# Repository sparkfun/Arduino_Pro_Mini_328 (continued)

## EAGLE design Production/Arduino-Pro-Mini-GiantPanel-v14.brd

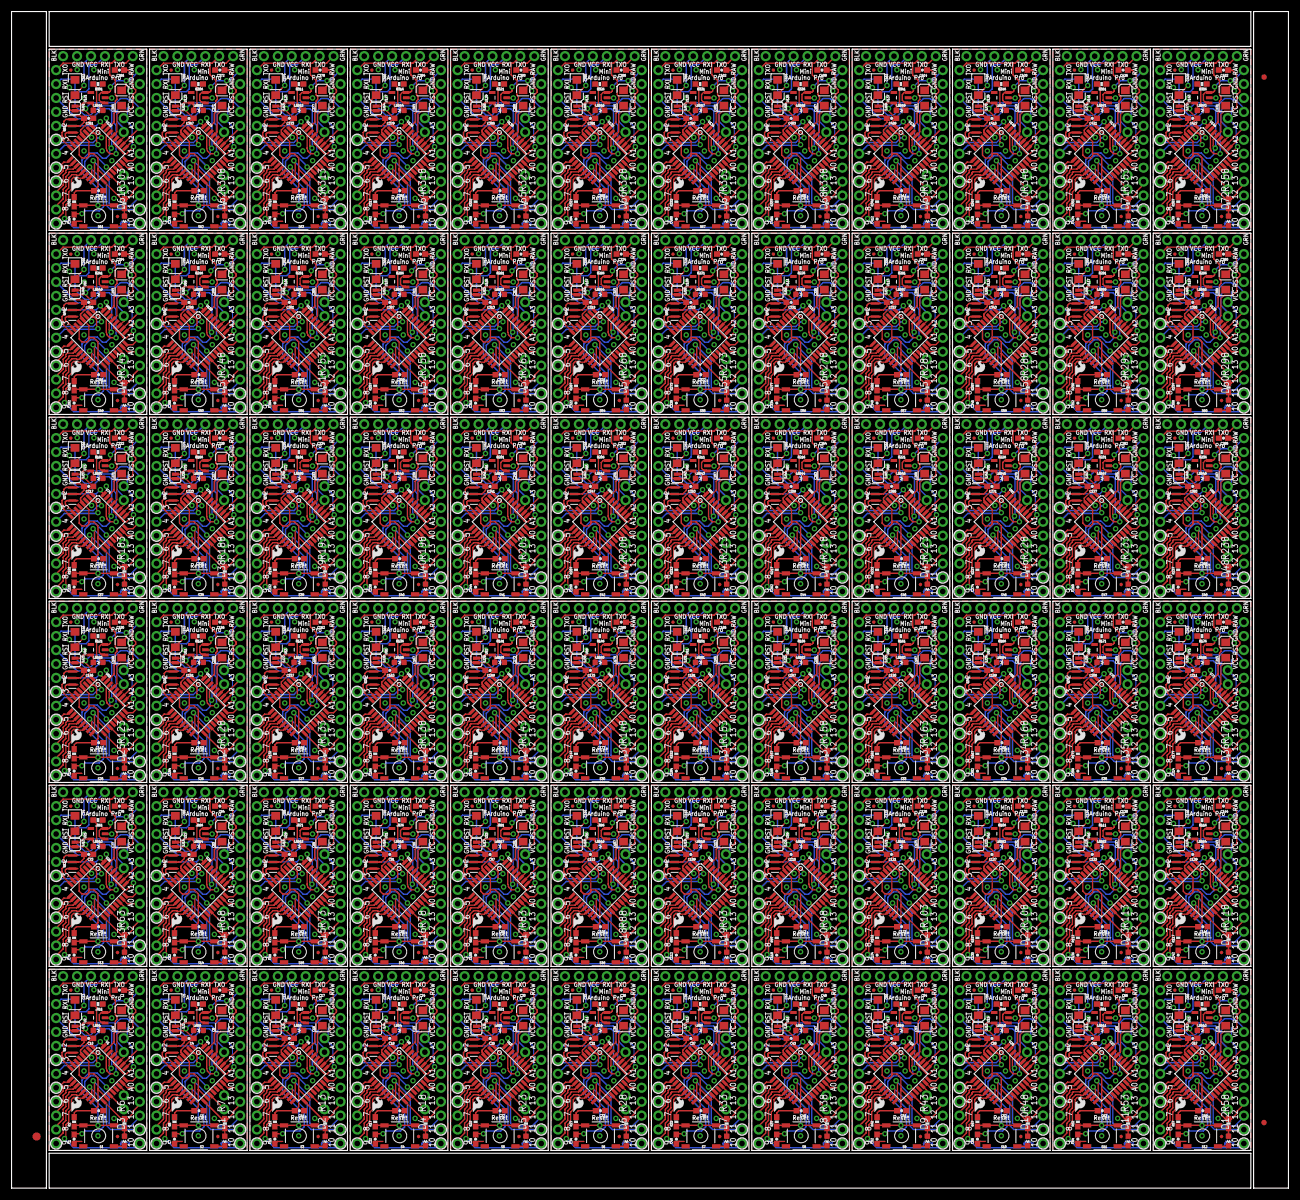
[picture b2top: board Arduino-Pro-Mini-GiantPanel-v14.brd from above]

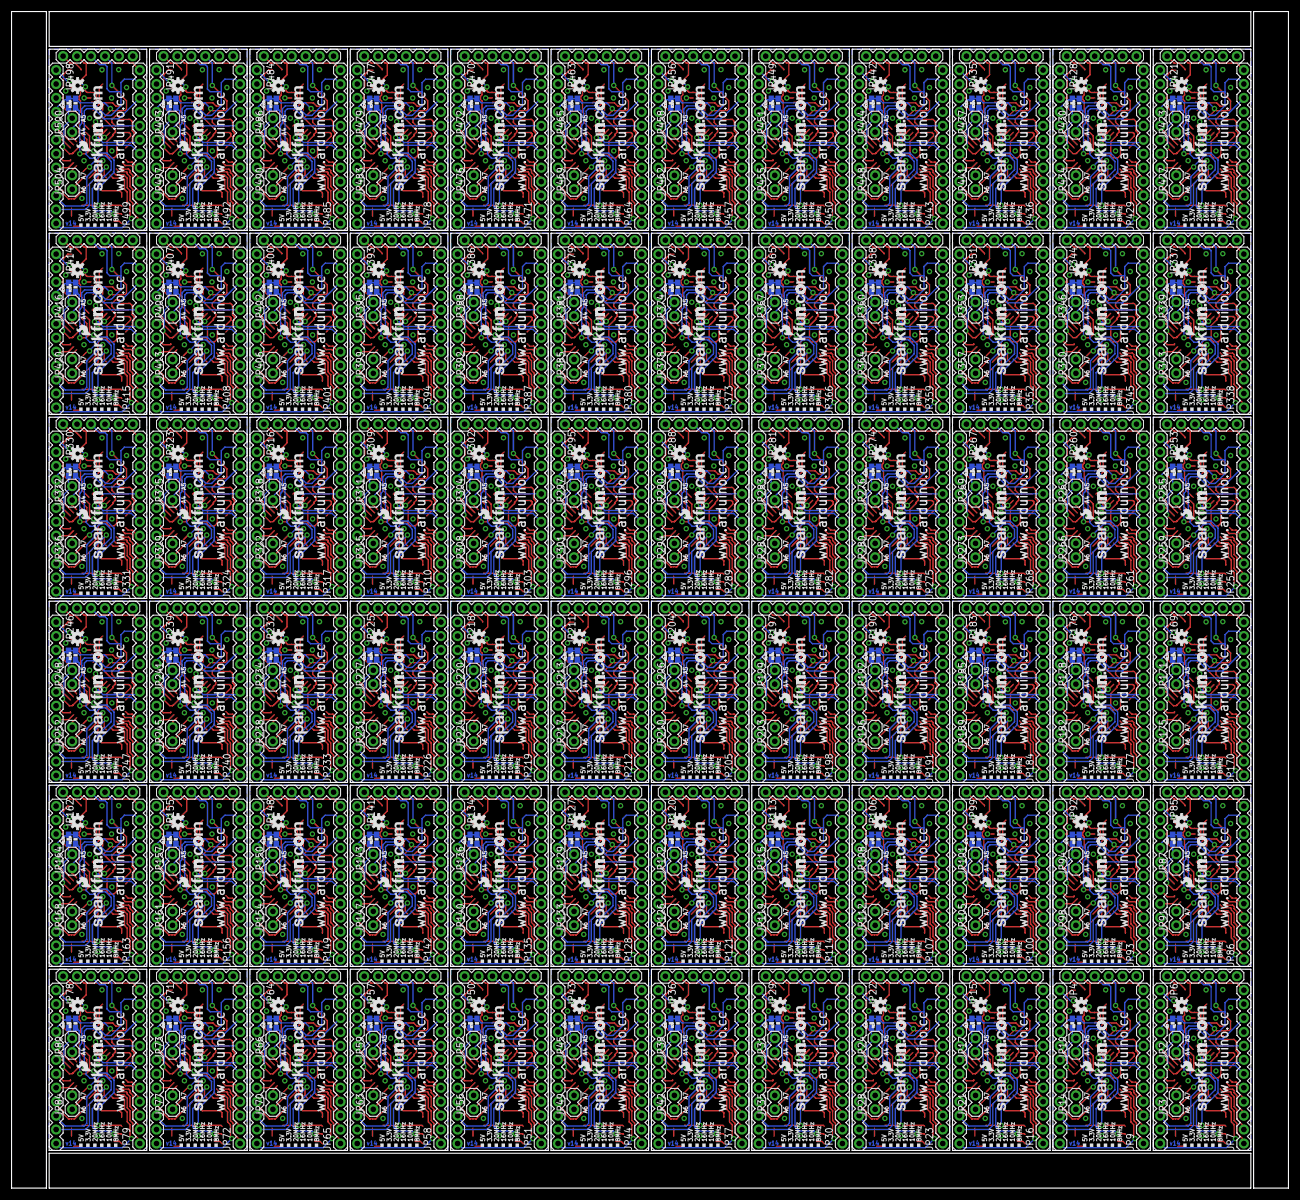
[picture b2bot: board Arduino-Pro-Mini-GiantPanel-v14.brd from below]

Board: 2 copper layers, 232.7 x 214.4 mm, 2019 parts (648 on the bottom side), 2376 nets.

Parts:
C1, C2, C3, C4, C6, C7, C9, C10, C11, C14, C15, C17, C18, C21, C22, C24, C25, C27, C28, C30, C31, C33, C34, C36, C37, C39, C40, C42, C43, C45, C46, C48, C49, C51, C52, C54, C55, C57, C58, C60, C61, C63, C64, C66, C67, C69, C70, C72, C73, C75, C76, C78, C79, C81, C82, C84, C85, C87, C88, C90, C91, C93, C94, C96, C97, C99, C100, C102, C103, C105, C106, C108, C109, C111, C112, C114, C115, C117, C118, C120, C121, C123, C124, C126, C127, C129, C130, C132, C133, C135, C136, C138, C139, C141, C142, C144, C145, C147, C148, C150, C151, C153, C154, C156, C157, C159, C160, C162, C163, C165, C166, C168, C169, C171, C172, C174, C175, C177, C178, C180, C181, C183, C184, C186, C187, C189, C190, C192, C193, C195, C196, C198, C199, C201, C202, C204, C205, C207, C208, C210, C211, C213, C214, C216, C217, C219, C220, C222, C223, C225, C226, C228, C229, C231, C232, C234, C235, C237, C238, C240, C241, C243, C244, C246, C247, C249, C250, C252, C253, C255, C256, C258, C259, C261, C262, C264, C265, C267, C268, C270, C271, C273, C274, C276, C277, C279, C280, C282, C283, C285, C286, C288, C289, C291, C292, C294, C295, C297, C298, C300, C301, C303, C304, C306, C307, C309, C310, C312, C313, C315, C316, C318, C319, C321, C322, C324, C325, C327, C328, C330, C331, C333, C334, C336, C337, C339, C340, C342, C343, C345, C346, C348, C349, C351, C352, C354, C355, C357, C358, C360, C361, C363, C364, C366, C367, C369, C370, C372, C373, C375, C376, C378, C379, C381, C382, C384, C385, C387, C388, C390, C391, C393, C394, C396, C397, C399, C400, C402, C403, C405, C406, C408, C409, C411, C412, C414, C415, C417, C418, C420, C421, C423, C424, C426, C427, C429, C430, C432: 0.1uF; 0603-CAP
C5, C8, C12, C13, C16, C19, C20, C23, C26, C29, C32, C35, C38, C41, C44, C47, C50, C53, C56, C59, C62, C65, C68, C71, C74, C77, C80, C83, C86, C89, C92, C95, C98, C101, C104, C107, C110, C113, C116, C119, C122, C125, C128, C131, C134, C137, C140, C143, C146, C149, C152, C155, C158, C161, C164, C167, C170, C173, C176, C179, C182, C185, C188, C191, C194, C197, C200, C203, C206, C209, C212, C215, C218, C221, C224, C227, C230, C233, C236, C239, C242, C245, C248, C251, C254, C257, C260, C263, C266, C269, C272, C275, C278, C281, C284, C287, C290, C293, C296, C299, C302, C305, C308, C311, C314, C317, C320, C323, C326, C329, C332, C335, C338, C341, C344, C347, C350, C353, C356, C359, C362, C365, C368, C371, C374, C377, C380, C383, C386, C389, C392, C395, C398, C401, C404, C407, C410, C413, C416, C419, C422, C425, C428, C431: 10uF; EIA3216
D1, D2, D3, D4, D5, D6, D7, D8, D9, D10, D11, D12, D13, D14, D15, D16, D17, D18, D19, D20, D21, D22, D23, D24, D25, D26, D27, D28, D29, D30, D31, D32, D33, D34, D35, D36, D37, D38, D39, D40, D41, D42, D43, D44, D45, D46, D47, D48, D49, D50, D51, D52, D53, D54, D55, D56, D57, D58, D59, D60, D61, D62, D63, D64, D65, D66, D67, D68, D69, D70, D71, D72: Green; 0603-LED-ALT1
E$1: FIDUCIAL-1.5X3
E$4, E$6: FIDUCIAL-1X2
JP1, JP11, JP18, JP25, JP32, JP39, JP46, JP53, JP60, JP67, JP74, JP81, JP88, JP95, JP102, JP109, JP116, JP123, JP130, JP137, JP144, JP151, JP158, JP165, JP172, JP179, JP186, JP193, JP200, JP207, JP214, JP221, JP228, JP235, JP242, JP249, JP256, JP263, JP270, JP277, JP284, JP291, JP298, JP305, JP312, JP319, JP326, JP333, JP340, JP347, JP354, JP361, JP368, JP375, JP382, JP389, JP396, JP403, JP410, JP417, JP424, JP431, JP438, JP445, JP452, JP459, JP466, JP473, JP480, JP487, JP494, JP501: FTDI Basic; 1X06
JP2, JP3, JP10, JP14, JP17, JP21, JP24, JP28, JP31, JP35, JP38, JP42, JP45, JP49, JP52, JP56, JP59, JP63, JP66, JP70, JP73, JP77, JP80, JP84, JP87, JP91, JP94, JP98, JP101, JP105, JP108, JP112, JP115, JP119, JP122, JP126, JP129, JP133, JP136, JP140, JP143, JP147, JP150, JP154, JP157, JP161, JP164, JP168, JP171, JP175, JP178, JP182, JP185, JP189, JP192, JP196, JP199, JP203, JP206, JP210, JP213, JP217, JP220, JP224, JP227, JP231, JP234, JP238, JP241, JP245, JP248, JP252, JP255, JP259, JP262, JP266, JP269, JP273, JP276, JP280, JP283, JP287, JP290, JP294, JP297, JP301, JP304, JP308, JP311, JP315, JP318, JP322, JP325, JP329, JP332, JP336, JP339, JP343, JP346, JP350, JP353, JP357, JP360, JP364, JP367, JP371, JP374, JP378, JP381, JP385, JP388, JP392, JP395, JP399, JP402, JP406, JP409, JP413, JP416, JP420, JP423, JP427, JP430, JP434, JP437, JP441, JP444, JP448, JP451, JP455, JP458, JP462, JP465, JP469, JP472, JP476, JP479, JP483, JP486, JP490, JP493, JP497, JP500, JP504: 1X02
JP4, JP6, JP7, JP9, JP15, JP16, JP22, JP23, JP29, JP30, JP36, JP37, JP43, JP44, JP50, JP51, JP57, JP58, JP64, JP65, JP71, JP72, JP78, JP79, JP85, JP86, JP92, JP93, JP99, JP100, JP106, JP107, JP113, JP114, JP120, JP121, JP127, JP128, JP134, JP135, JP141, JP142, JP148, JP149, JP155, JP156, JP162, JP163, JP169, JP170, JP176, JP177, JP183, JP184, JP190, JP191, JP197, JP198, JP204, JP205, JP211, JP212, JP218, JP219, JP225, JP226, JP232, JP233, JP239, JP240, JP246, JP247, JP253, JP254, JP260, JP261, JP267, JP268, JP274, JP275, JP281, JP282, JP288, JP289, JP295, JP296, JP302, JP303, JP309, JP310, JP316, JP317, JP323, JP324, JP330, JP331, JP337, JP338, JP344, JP345, JP351, JP352, JP358, JP359, JP365, JP366, JP372, JP373, JP379, JP380, JP386, JP387, JP393, JP394, JP400, JP401, JP407, JP408, JP414, JP415, JP421, JP422, JP428, JP429, JP435, JP436, JP442, JP443, JP449, JP450, JP456, JP457, JP463, JP464, JP470, JP471, JP477, JP478, JP484, JP485, JP491, JP492, JP498, JP499: 1X12
JP5, JP8, JP12, JP13, JP19, JP20, JP26, JP27, JP33, JP34, JP40, JP41, JP47, JP48, JP54, JP55, JP61, JP62, JP68, JP69, JP75, JP76, JP82, JP83, JP89, JP90, JP96, JP97, JP103, JP104, JP110, JP111, JP117, JP118, JP124, JP125, JP131, JP132, JP138, JP139, JP145, JP146, JP152, JP153, JP159, JP160, JP166, JP167, JP173, JP174, JP180, JP181, JP187, JP188, JP194, JP195, JP201, JP202, JP208, JP209, JP215, JP216, JP222, JP223, JP229, JP230, JP236, JP237, JP243, JP244, JP250, JP251, JP257, JP258, JP264, JP265, JP271, JP272, JP278, JP279, JP285, JP286, JP292, JP293, JP299, JP300, JP306, JP307, JP313, JP314, JP320, JP321, JP327, JP328, JP334, JP335, JP341, JP342, JP348, JP349, JP355, JP356, JP362, JP363, JP369, JP370, JP376, JP377, JP383, JP384, JP390, JP391, JP397, JP398, JP404, JP405, JP411, JP412, JP418, JP419, JP425, JP426, JP432, JP433, JP439, JP440, JP446, JP447, JP453, JP454, JP460, JP461, JP467, JP468, JP474, JP475, JP481, JP482, JP488, JP489, JP495, JP496, JP502, JP503: FIDUCIALUFIDUCIAL; MICRO-FIDUCIAL
LED1, LED2, LED3, LED4, LED5, LED6, LED7, LED8, LED9, LED10, LED11, LED12, LED13, LED14, LED15, LED16, LED17, LED18, LED19, LED20, LED21, LED22, LED23, LED24, LED25, LED26, LED27, LED28, LED29, LED30, LED31, LED32, LED33, LED34, LED35, LED36, LED37, LED38, LED39, LED40, LED41, LED42, LED43, LED44, LED45, LED46, LED47, LED48, LED49, LED50, LED51, LED52, LED53, LED54, LED55, LED56, LED57, LED58, LED59, LED60, LED61, LED62, LED63, LED64, LED65, LED66, LED67, LED68, LED69, LED70, LED71, LED72: Red; 0603-LED-ALT1
Q1, Q2, Q3, Q4, Q5, Q6, Q7, Q8, Q9, Q10, Q11, Q12, Q13, Q14, Q15, Q16, Q17, Q18, Q19, Q20, Q21, Q22, Q23, Q24, Q25, Q26, Q27, Q28, Q29, Q30, Q31, Q32, Q33, Q34, Q35, Q36, Q37, Q38, Q39, Q40, Q41, Q42, Q43, Q44, Q45, Q46, Q47, Q48, Q49, Q50, Q51, Q52, Q53, Q54, Q55, Q56, Q57, Q58, Q59, Q60, Q61, Q62, Q63, Q64, Q65, Q66, Q67, Q68, Q69, Q70, Q71, Q72: 8/16/20MHz; RESONATOR-SMD-1:1
R1, R3, R8, R9, R14, R15, R19, R20, R24, R25, R29, R30, R34, R35, R39, R40, R44, R45, R49, R50, R54, R55, R59, R60, R64, R65, R69, R70, R74, R75, R79, R80, R84, R85, R89, R90, R94, R95, R99, R100, R104, R105, R109, R110, R114, R115, R119, R120, R124, R125, R129, R130, R134, R135, R139, R140, R144, R145, R149, R150, R154, R155, R159, R160, R164, R165, R169, R170, R174, R175, R179, R180, R184, R185, R189, R190, R194, R195, R199, R200, R204, R205, R209, R210, R214, R215, R219, R220, R224, R225, R229, R230, R234, R235, R239, R240, R244, R245, R249, R250, R254, R255, R259, R260, R264, R265, R269, R270, R274, R275, R279, R280, R284, R285, R289, R290, R294, R295, R299, R300, R304, R305, R309, R310, R314, R315, R319, R320, R324, R325, R329, R330, R334, R335, R339, R340, R344, R345, R349, R350, R354, R355, R359, R360: 0603-RES
R2, R4, R5, R10, R11, R12, R16, R17, R21, R22, R26, R27, R31, R32, R36, R37, R41, R42, R46, R47, R51, R52, R56, R57, R61, R62, R66, R67, R71, R72, R76, R77, R81, R82, R86, R87, R91, R92, R96, R97, R101, R102, R106, R107, R111, R112, R116, R117, R121, R122, R126, R127, R131, R132, R136, R137, R141, R142, R146, R147, R151, R152, R156, R157, R161, R162, R166, R167, R171, R172, R176, R177, R181, R182, R186, R187, R191, R192, R196, R197, R201, R202, R206, R207, R211, R212, R216, R217, R221, R222, R226, R227, R231, R232, R236, R237, R241, R242, R246, R247, R251, R252, R256, R257, R261, R262, R266, R267, R271, R272, R276, R277, R281, R282, R286, R287, R291, R292, R296, R297, R301, R302, R306, R307, R311, R312, R316, R317, R321, R322, R326, R327, R331, R332, R336, R337, R341, R342, R346, R347, R351, R352, R356, R357: 10K; 0603-RES
R6, R7, R13, R18, R23, R28, R33, R38, R43, R48, R53, R58, R63, R68, R73, R78, R83, R88, R93, R98, R103, R108, R113, R118, R123, R128, R133, R138, R143, R148, R153, R158, R163, R168, R173, R178, R183, R188, R193, R198, R203, R208, R213, R218, R223, R228, R233, R238, R243, R248, R253, R258, R263, R268, R273, R278, R283, R288, R293, R298, R303, R308, R313, R318, R323, R328, R333, R338, R343, R348, R353, R358: 330; 0603-RES
S1, S2, S3, S4, S5, S6, S7, S8, S9, S10, S11, S12, S13, S14, S15, S16, S17, S18, S19, S20, S21, S22, S23, S24, S25, S26, S27, S28, S29, S30, S31, S32, S33, S34, S35, S36, S37, S38, S39, S40, S41, S42, S43, S44, S45, S46, S47, S48, S49, S50, S51, S52, S53, S54, S55, S56, S57, S58, S59, S60, S61, S62, S63, S64, S65, S66, S67, S68, S69, S70, S71, S72: Reset; TACTILE-SWITCH-SMD-ALT01
SJ1, SJ2, SJ3, SJ4, SJ5, SJ6, SJ7, SJ8, SJ9, SJ10, SJ11, SJ12, SJ13, SJ14, SJ15, SJ16, SJ17, SJ18, SJ19, SJ20, SJ21, SJ22, SJ23, SJ24, SJ25, SJ26, SJ27, SJ28, SJ29, SJ30, SJ31, SJ32, SJ33, SJ34, SJ35, SJ36, SJ37, SJ38, SJ39, SJ40, SJ41, SJ42, SJ43, SJ44, SJ45, SJ46, SJ47, SJ48, SJ49, SJ50, SJ51, SJ52, SJ53, SJ54, SJ55, SJ56, SJ57, SJ58, SJ59, SJ60, SJ61, SJ62, SJ63, SJ64, SJ65, SJ66, SJ67, SJ68, SJ69, SJ70, SJ71, SJ72: SJ_2S
U1, U4, U6, U8, U10, U12, U14, U16, U18, U20, U22, U24, U26, U28, U30, U32, U34, U36, U38, U40, U42, U44, U46, U48, U50, U52, U54, U56, U58, U60, U62, U64, U66, U68, U70, U72, U74, U76, U78, U80, U82, U84, U86, U88, U90, U92, U94, U96, U98, U100, U102, U104, U106, U108, U110, U112, U114, U116, U118, U120, U122, U124, U126, U128, U130, U132, U134, U136, U138, U140, U142, U144: ATMEGA328; TQFP32-08
U2, U3, U5, U7, U9, U11, U13, U15, U17, U19, U21, U23, U25, U27, U29, U31, U33, U35, U37, U39, U41, U43, U45, U47, U49, U51, U53, U55, U57, U59, U61, U63, U65, U67, U69, U71, U73, U75, U77, U79, U81, U83, U85, U87, U89, U91, U93, U95, U97, U99, U101, U103, U105, U107, U109, U111, U113, U115, U117, U119, U121, U123, U125, U127, U129, U131, U133, U135, U137, U139, U141, U143: MIC5205; SOT23-5
U$1, U$4, U$7, U$10, U$14, U$17, U$20, U$23, U$26, U$29, U$32, U$35, U$38, U$41, U$44, U$47, U$50, U$53, U$56, U$59, U$62, U$65, U$68, U$71, U$74, U$77, U$80, U$83, U$86, U$89, U$92, U$95, U$98, U$101, U$104, U$107, U$110, U$113, U$116, U$119, U$122, U$125, U$128, U$131, U$134, U$137, U$140, U$143, U$146, U$149, U$152, U$155, U$158, U$161, U$164, U$167, U$170, U$173, U$176, U$179, U$182, U$185, U$188, U$191, U$194, U$197, U$200, U$203, U$206, U$209, U$212, U$215: LOGO-SFESK; SFE-LOGO-FLAME
U$2, U$6, U$9, U$11, U$13, U$16, U$19, U$22, U$25, U$28, U$31, U$34, U$37, U$40, U$43, U$46, U$49, U$52, U$55, U$58, U$61, U$64, U$67, U$70, U$73, U$76, U$79, U$82, U$85, U$88, U$91, U$94, U$97, U$100, U$103, U$106, U$109, U$112, U$115, U$118, U$121, U$124, U$127, U$130, U$133, U$136, U$139, U$142, U$145, U$148, U$151, U$154, U$157, U$160, U$163, U$166, U$169, U$172, U$175, U$178, U$181, U$184, U$187, U$190, U$193, U$196, U$199, U$202, U$205, U$208, U$211, U$214: LOGO-SFENEW; SFE-NEW-WEBLOGO
U$3, U$5, U$8, U$12, U$15, U$18, U$21, U$24, U$27, U$30, U$33, U$36, U$39, U$42, U$45, U$48, U$51, U$54, U$57, U$60, U$63, U$66, U$69, U$72, U$75, U$78, U$81, U$84, U$87, U$90, U$93, U$96, U$99, U$102, U$105, U$108, U$111, U$114, U$117, U$120, U$123, U$126, U$129, U$132, U$135, U$138, U$141, U$144, U$147, U$150, U$153, U$156, U$159, U$162, U$165, U$168, U$171, U$174, U$177, U$180, U$183, U$186, U$189, U$192, U$195, U$198, U$201, U$204, U$207, U$210, U$213, U$216: OSHW-LOGOS; OSHW-LOGO-S

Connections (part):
A0: JP6.8, U1.23
A1: JP6.7, U1.24
A2: JP6.6, U1.25
A3: JP6.5, U1.26
A4: JP2.1, R1.1, U1.27
A5: JP2.2, R3.1, U1.28
A6: JP3.1, U1.19
A7: JP3.2, U1.22
A8: JP10.2, R9.1, U4.28
A9: JP10.1, R8.1, U4.27
A10: JP4.5, U4.26
A11: JP4.6, U4.25
A12: JP4.7, U4.24
A13: JP4.8, U4.23
A14: JP14.1, U4.19
A15: JP14.2, U4.22
A16: JP17.2, R15.1, U6.28
A17: JP17.1, R14.1, U6.27
A18: JP15.5, U6.26
A19: JP15.6, U6.25
A20: JP15.7, U6.24
A21: JP15.8, U6.23
A22: JP21.1, U6.19
A23: JP21.2, U6.22
A24: JP24.2, R20.1, U8.28
A25: JP24.1, R19.1, U8.27
A26: JP22.5, U8.26
A27: JP22.6, U8.25
A28: JP22.7, U8.24
A29: JP22.8, U8.23
A30: JP28.1, U8.19
A31: JP28.2, U8.22
A32: JP31.2, R25.1, U10.28
A33: JP31.1, R24.1, U10.27
A34: JP29.5, U10.26
A35: JP29.6, U10.25
A36: JP29.7, U10.24
A37: JP29.8, U10.23
A38: JP35.1, U10.19
A39: JP35.2, U10.22
A40: JP38.2, R30.1, U12.28
A41: JP38.1, R29.1, U12.27
A42: JP36.5, U12.26
A43: JP36.6, U12.25
A44: JP36.7, U12.24
A45: JP36.8, U12.23
A46: JP42.1, U12.19
A47: JP42.2, U12.22
A48: JP45.2, R35.1, U14.28
A49: JP45.1, R34.1, U14.27
A50: JP43.5, U14.26
A51: JP43.6, U14.25
A52: JP43.7, U14.24
A53: JP43.8, U14.23
A54: JP49.1, U14.19
A55: JP49.2, U14.22
A56: JP52.2, R40.1, U16.28
A57: JP52.1, R39.1, U16.27
A58: JP50.5, U16.26
A59: JP50.6, U16.25
A60: JP50.7, U16.24
A61: JP50.8, U16.23
A62: JP56.1, U16.19
A63: JP56.2, U16.22
A64: JP59.2, R45.1, U18.28
A65: JP59.1, R44.1, U18.27
A66: JP57.5, U18.26
A67: JP57.6, U18.25
A68: JP57.7, U18.24
A69: JP57.8, U18.23
A70: JP63.1, U18.19
A71: JP63.2, U18.22
A72: JP66.2, R50.1, U20.28
A73: JP66.1, R49.1, U20.27
A74: JP64.5, U20.26
A75: JP64.6, U20.25
A76: JP64.7, U20.24
A77: JP64.8, U20.23
A78: JP70.1, U20.19
A79: JP70.2, U20.22
A80: JP73.2, R55.1, U22.28
A81: JP73.1, R54.1, U22.27
A82: JP71.5, U22.26
A83: JP71.6, U22.25
A84: JP71.7, U22.24
A85: JP71.8, U22.23
A86: JP77.1, U22.19
A87: JP77.2, U22.22
A88: JP80.2, R60.1, U24.28
A89: JP80.1, R59.1, U24.27
A90: JP78.5, U24.26
A91: JP78.6, U24.25
A92: JP78.7, U24.24
A93: JP78.8, U24.23
A94: JP84.1, U24.19
A95: JP84.2, U24.22
A96: JP87.2, R65.1, U26.28
A97: JP87.1, R64.1, U26.27
A98: JP85.5, U26.26
A99: JP85.6, U26.25
A100: JP85.7, U26.24
A101: JP85.8, U26.23
A102: JP91.1, U26.19
A103: JP91.2, U26.22
A104: JP94.2, R70.1, U28.28
A105: JP94.1, R69.1, U28.27
A106: JP92.5, U28.26
A107: JP92.6, U28.25
A108: JP92.7, U28.24
A109: JP92.8, U28.23
A110: JP98.1, U28.19
A111: JP98.2, U28.22
A112: JP101.2, R75.1, U30.28
A113: JP101.1, R74.1, U30.27
A114: JP99.5, U30.26
A115: JP99.6, U30.25
A116: JP99.7, U30.24
A117: JP99.8, U30.23
A118: JP105.1, U30.19
A119: JP105.2, U30.22
A120: JP108.2, R80.1, U32.28
A121: JP108.1, R79.1, U32.27
A122: JP106.5, U32.26
A123: JP106.6, U32.25
A124: JP106.7, U32.24
A125: JP106.8, U32.23
A126: JP112.1, U32.19
A127: JP112.2, U32.22
A128: JP115.2, R85.1, U34.28
A129: JP115.1, R84.1, U34.27
A130: JP113.5, U34.26
A131: JP113.6, U34.25
A132: JP113.7, U34.24
A133: JP113.8, U34.23
A134: JP119.1, U34.19
A135: JP119.2, U34.22
A136: JP122.2, R90.1, U36.28
A137: JP122.1, R89.1, U36.27
A138: JP120.5, U36.26
A139: JP120.6, U36.25
A140: JP120.7, U36.24
A141: JP120.8, U36.23
A142: JP126.1, U36.19
A143: JP126.2, U36.22
A144: JP129.2, R95.1, U38.28
A145: JP129.1, R94.1, U38.27
A146: JP127.5, U38.26
A147: JP127.6, U38.25
A148: JP127.7, U38.24
A149: JP127.8, U38.23
A150: JP133.1, U38.19
A151: JP133.2, U38.22
A152: JP136.2, R100.1, U40.28
A153: JP136.1, R99.1, U40.27
A154: JP134.5, U40.26
A155: JP134.6, U40.25
A156: JP134.7, U40.24
A157: JP134.8, U40.23
A158: JP140.1, U40.19
A159: JP140.2, U40.22
A160: JP143.2, R105.1, U42.28
A161: JP143.1, R104.1, U42.27
A162: JP141.5, U42.26
A163: JP141.6, U42.25
A164: JP141.7, U42.24
A165: JP141.8, U42.23
A166: JP147.1, U42.19
A167: JP147.2, U42.22
A168: JP150.2, R110.1, U44.28
A169: JP150.1, R109.1, U44.27
A170: JP148.5, U44.26
A171: JP148.6, U44.25
A172: JP148.7, U44.24
A173: JP148.8, U44.23
A174: JP154.1, U44.19
A175: JP154.2, U44.22
A176: JP157.2, R115.1, U46.28
A177: JP157.1, R114.1, U46.27
A178: JP155.5, U46.26
A179: JP155.6, U46.25
A180: JP155.7, U46.24
A181: JP155.8, U46.23
A182: JP161.1, U46.19
A183: JP161.2, U46.22
A184: JP164.2, R120.1, U48.28
A185: JP164.1, R119.1, U48.27
A186: JP162.5, U48.26
A187: JP162.6, U48.25
A188: JP162.7, U48.24
A189: JP162.8, U48.23
A190: JP168.1, U48.19
A191: JP168.2, U48.22
A192: JP171.2, R125.1, U50.28
A193: JP171.1, R124.1, U50.27
A194: JP169.5, U50.26
A195: JP169.6, U50.25
A196: JP169.7, U50.24
A197: JP169.8, U50.23
A198: JP175.1, U50.19
A199: JP175.2, U50.22
A200: JP178.2, R130.1, U52.28
A201: JP178.1, R129.1, U52.27
A202: JP176.5, U52.26
A203: JP176.6, U52.25
A204: JP176.7, U52.24
A205: JP176.8, U52.23
A206: JP182.1, U52.19
A207: JP182.2, U52.22
A208: JP185.2, R135.1, U54.28
A209: JP185.1, R134.1, U54.27
A210: JP183.5, U54.26
A211: JP183.6, U54.25
A212: JP183.7, U54.24
A213: JP183.8, U54.23
A214: JP189.1, U54.19
A215: JP189.2, U54.22
A216: JP192.2, R140.1, U56.28
A217: JP192.1, R139.1, U56.27
A218: JP190.5, U56.26
A219: JP190.6, U56.25
A220: JP190.7, U56.24
A221: JP190.8, U56.23
A222: JP196.1, U56.19
A223: JP196.2, U56.22
A224: JP199.2, R145.1, U58.28
A225: JP199.1, R144.1, U58.27
A226: JP197.5, U58.26
A227: JP197.6, U58.25
A228: JP197.7, U58.24
A229: JP197.8, U58.23
A230: JP203.1, U58.19
A231: JP203.2, U58.22
A232: JP206.2, R150.1, U60.28
A233: JP206.1, R149.1, U60.27
A234: JP204.5, U60.26
A235: JP204.6, U60.25
A236: JP204.7, U60.24
A237: JP204.8, U60.23
A238: JP210.1, U60.19
A239: JP210.2, U60.22
A240: JP213.2, R155.1, U62.28
A241: JP213.1, R154.1, U62.27
A242: JP211.5, U62.26
A243: JP211.6, U62.25
A244: JP211.7, U62.24
A245: JP211.8, U62.23
A246: JP217.1, U62.19
A247: JP217.2, U62.22
A248: JP220.2, R160.1, U64.28
A249: JP220.1, R159.1, U64.27
A250: JP218.5, U64.26
A251: JP218.6, U64.25
A252: JP218.7, U64.24
A253: JP218.8, U64.23
A254: JP224.1, U64.19
A255: JP224.2, U64.22
A256: JP227.2, R165.1, U66.28
A257: JP227.1, R164.1, U66.27
A258: JP225.5, U66.26
A259: JP225.6, U66.25
A260: JP225.7, U66.24
A261: JP225.8, U66.23
A262: JP231.1, U66.19
A263: JP231.2, U66.22
A264: JP234.2, R170.1, U68.28
A265: JP234.1, R169.1, U68.27
A266: JP232.5, U68.26
A267: JP232.6, U68.25
A268: JP232.7, U68.24
A269: JP232.8, U68.23
A270: JP238.1, U68.19
A271: JP238.2, U68.22
A272: JP241.2, R175.1, U70.28
A273: JP241.1, R174.1, U70.27
A274: JP239.5, U70.26
A275: JP239.6, U70.25
A276: JP239.7, U70.24
A277: JP239.8, U70.23
A278: JP245.1, U70.19
A279: JP245.2, U70.22
A280: JP248.2, R180.1, U72.28
A281: JP248.1, R179.1, U72.27
A282: JP246.5, U72.26
A283: JP246.6, U72.25
A284: JP246.7, U72.24
A285: JP246.8, U72.23
A286: JP252.1, U72.19
A287: JP252.2, U72.22
A288: JP255.2, R185.1, U74.28
A289: JP255.1, R184.1, U74.27
A290: JP253.5, U74.26
A291: JP253.6, U74.25
A292: JP253.7, U74.24
A293: JP253.8, U74.23
A294: JP259.1, U74.19
A295: JP259.2, U74.22
A296: JP262.2, R190.1, U76.28
A297: JP262.1, R189.1, U76.27
A298: JP260.5, U76.26
A299: JP260.6, U76.25
A300: JP260.7, U76.24
A301: JP260.8, U76.23
A302: JP266.1, U76.19
A303: JP266.2, U76.22
A304: JP269.2, R195.1, U78.28
A305: JP269.1, R194.1, U78.27
A306: JP267.5, U78.26
A307: JP267.6, U78.25
A308: JP267.7, U78.24
A309: JP267.8, U78.23
A310: JP273.1, U78.19
A311: JP273.2, U78.22
A312: JP276.2, R200.1, U80.28
A313: JP276.1, R199.1, U80.27
A314: JP274.5, U80.26
A315: JP274.6, U80.25
A316: JP274.7, U80.24
A317: JP274.8, U80.23
A318: JP280.1, U80.19
A319: JP280.2, U80.22
A320: JP283.2, R205.1, U82.28
A321: JP283.1, R204.1, U82.27
A322: JP281.5, U82.26
A323: JP281.6, U82.25
A324: JP281.7, U82.24
A325: JP281.8, U82.23
A326: JP287.1, U82.19
A327: JP287.2, U82.22
A328: JP290.2, R210.1, U84.28
A329: JP290.1, R209.1, U84.27
A330: JP288.5, U84.26
A331: JP288.6, U84.25
A332: JP288.7, U84.24
A333: JP288.8, U84.23
A334: JP294.1, U84.19
A335: JP294.2, U84.22
A336: JP297.2, R215.1, U86.28
A337: JP297.1, R214.1, U86.27
A338: JP295.5, U86.26
A339: JP295.6, U86.25
A340: JP295.7, U86.24
A341: JP295.8, U86.23
A342: JP301.1, U86.19
A343: JP301.2, U86.22
A344: JP304.2, R220.1, U88.28
A345: JP304.1, R219.1, U88.27
A346: JP302.5, U88.26
A347: JP302.6, U88.25
A348: JP302.7, U88.24
A349: JP302.8, U88.23
A350: JP308.1, U88.19
A351: JP308.2, U88.22
A352: JP311.2, R225.1, U90.28
A353: JP311.1, R224.1, U90.27
A354: JP309.5, U90.26
A355: JP309.6, U90.25
A356: JP309.7, U90.24
A357: JP309.8, U90.23
A358: JP315.1, U90.19
A359: JP315.2, U90.22
A360: JP318.2, R230.1, U92.28
A361: JP318.1, R229.1, U92.27
A362: JP316.5, U92.26
A363: JP316.6, U92.25
A364: JP316.7, U92.24
A365: JP316.8, U92.23
A366: JP322.1, U92.19
A367: JP322.2, U92.22
A368: JP325.2, R235.1, U94.28
A369: JP325.1, R234.1, U94.27
A370: JP323.5, U94.26
A371: JP323.6, U94.25
A372: JP323.7, U94.24
A373: JP323.8, U94.23
A374: JP329.1, U94.19
A375: JP329.2, U94.22
A376: JP332.2, R240.1, U96.28
A377: JP332.1, R239.1, U96.27
A378: JP330.5, U96.26
A379: JP330.6, U96.25
A380: JP330.7, U96.24
A381: JP330.8, U96.23
A382: JP336.1, U96.19
A383: JP336.2, U96.22
A384: JP339.2, R245.1, U98.28
A385: JP339.1, R244.1, U98.27
A386: JP337.5, U98.26
A387: JP337.6, U98.25
A388: JP337.7, U98.24
A389: JP337.8, U98.23
A390: JP343.1, U98.19
A391: JP343.2, U98.22
A392: JP346.2, R250.1, U100.28
A393: JP346.1, R249.1, U100.27
A394: JP344.5, U100.26
A395: JP344.6, U100.25
A396: JP344.7, U100.24
A397: JP344.8, U100.23
A398: JP350.1, U100.19
A399: JP350.2, U100.22
A400: JP353.2, R255.1, U102.28
A401: JP353.1, R254.1, U102.27
A402: JP351.5, U102.26
A403: JP351.6, U102.25
A404: JP351.7, U102.24
A405: JP351.8, U102.23
A406: JP357.1, U102.19
A407: JP357.2, U102.22
A408: JP360.2, R260.1, U104.28
A409: JP360.1, R259.1, U104.27
A410: JP358.5, U104.26
A411: JP358.6, U104.25
A412: JP358.7, U104.24
A413: JP358.8, U104.23
A414: JP364.1, U104.19
A415: JP364.2, U104.22
A416: JP367.2, R265.1, U106.28
A417: JP367.1, R264.1, U106.27
A418: JP365.5, U106.26
A419: JP365.6, U106.25
A420: JP365.7, U106.24
A421: JP365.8, U106.23
A422: JP371.1, U106.19
A423: JP371.2, U106.22
A424: JP374.2, R270.1, U108.28
A425: JP374.1, R269.1, U108.27
A426: JP372.5, U108.26
A427: JP372.6, U108.25
A428: JP372.7, U108.24
A429: JP372.8, U108.23
A430: JP378.1, U108.19
A431: JP378.2, U108.22
A432: JP381.2, R275.1, U110.28
A433: JP381.1, R274.1, U110.27
A434: JP379.5, U110.26
A435: JP379.6, U110.25
A436: JP379.7, U110.24
A437: JP379.8, U110.23
A438: JP385.1, U110.19
A439: JP385.2, U110.22
A440: JP388.2, R280.1, U112.28
A441: JP388.1, R279.1, U112.27
A442: JP386.5, U112.26
A443: JP386.6, U112.25
A444: JP386.7, U112.24
A445: JP386.8, U112.23
A446: JP392.1, U112.19
A447: JP392.2, U112.22
A448: JP395.2, R285.1, U114.28
A449: JP395.1, R284.1, U114.27
A450: JP393.5, U114.26
A451: JP393.6, U114.25
A452: JP393.7, U114.24
A453: JP393.8, U114.23
A454: JP399.1, U114.19
A455: JP399.2, U114.22
A456: JP402.2, R290.1, U116.28
A457: JP402.1, R289.1, U116.27
A458: JP400.5, U116.26
A459: JP400.6, U116.25
A460: JP400.7, U116.24
A461: JP400.8, U116.23
A462: JP406.1, U116.19
A463: JP406.2, U116.22
A464: JP409.2, R295.1, U118.28
A465: JP409.1, R294.1, U118.27
A466: JP407.5, U118.26
A467: JP407.6, U118.25
A468: JP407.7, U118.24
A469: JP407.8, U118.23
A470: JP413.1, U118.19
A471: JP413.2, U118.22
A472: JP416.2, R300.1, U120.28
A473: JP416.1, R299.1, U120.27
A474: JP414.5, U120.26
A475: JP414.6, U120.25
A476: JP414.7, U120.24
A477: JP414.8, U120.23
A478: JP420.1, U120.19
A479: JP420.2, U120.22
A480: JP423.2, R305.1, U122.28
A481: JP423.1, R304.1, U122.27
A482: JP421.5, U122.26
A483: JP421.6, U122.25
A484: JP421.7, U122.24
A485: JP421.8, U122.23
A486: JP427.1, U122.19
A487: JP427.2, U122.22
A488: JP430.2, R310.1, U124.28
A489: JP430.1, R309.1, U124.27
A490: JP428.5, U124.26
A491: JP428.6, U124.25
A492: JP428.7, U124.24
A493: JP428.8, U124.23
A494: JP434.1, U124.19
A495: JP434.2, U124.22
A496: JP437.2, R315.1, U126.28
A497: JP437.1, R314.1, U126.27
A498: JP435.5, U126.26
A499: JP435.6, U126.25
A500: JP435.7, U126.24
A501: JP435.8, U126.23
A502: JP441.1, U126.19
A503: JP441.2, U126.22
A504: JP444.2, R320.1, U128.28
A505: JP444.1, R319.1, U128.27
A506: JP442.5, U128.26
A507: JP442.6, U128.25
A508: JP442.7, U128.24
A509: JP442.8, U128.23
A510: JP448.1, U128.19
A511: JP448.2, U128.22
A512: JP451.2, R325.1, U130.28
A513: JP451.1, R324.1, U130.27
A514: JP449.5, U130.26
A515: JP449.6, U130.25
A516: JP449.7, U130.24
A517: JP449.8, U130.23
A518: JP455.1, U130.19
A519: JP455.2, U130.22
A520: JP458.2, R330.1, U132.28
A521: JP458.1, R329.1, U132.27
A522: JP456.5, U132.26
A523: JP456.6, U132.25
A524: JP456.7, U132.24
A525: JP456.8, U132.23
A526: JP462.1, U132.19
A527: JP462.2, U132.22
A528: JP465.2, R335.1, U134.28
A529: JP465.1, R334.1, U134.27
A530: JP463.5, U134.26
A531: JP463.6, U134.25
A532: JP463.7, U134.24
A533: JP463.8, U134.23
A534: JP469.1, U134.19
A535: JP469.2, U134.22
A536: JP472.2, R340.1, U136.28
A537: JP472.1, R339.1, U136.27
A538: JP470.5, U136.26
A539: JP470.6, U136.25
A540: JP470.7, U136.24
A541: JP470.8, U136.23
A542: JP476.1, U136.19
A543: JP476.2, U136.22
A544: JP479.2, R345.1, U138.28
A545: JP479.1, R344.1, U138.27
A546: JP477.5, U138.26
A547: JP477.6, U138.25
A548: JP477.7, U138.24
A549: JP477.8, U138.23
A550: JP483.1, U138.19
A551: JP483.2, U138.22
A552: JP486.2, R350.1, U140.28
A553: JP486.1, R349.1, U140.27
A554: JP484.5, U140.26
A555: JP484.6, U140.25
A556: JP484.7, U140.24
A557: JP484.8, U140.23
A558: JP490.1, U140.19
A559: JP490.2, U140.22
A560: JP493.2, R355.1, U142.28
A561: JP493.1, R354.1, U142.27
A562: JP491.5, U142.26
A563: JP491.6, U142.25
A564: JP491.7, U142.24
A565: JP491.8, U142.23
A566: JP497.1, U142.19
A567: JP497.2, U142.22
A568: JP500.2, R360.1, U144.28
A569: JP500.1, R359.1, U144.27
A570: JP498.5, U144.26
A571: JP498.6, U144.25
A572: JP498.7, U144.24
A573: JP498.8, U144.23
A574: JP504.1, U144.19
A575: JP504.2, U144.22
AREF: C1.2, U1.20
AREF1: C7.2, U4.20
AREF2: C15.2, U6.20
AREF3: C22.2, U8.20
AREF4: C28.2, U10.20
AREF5: C34.2, U12.20
AREF6: C40.2, U14.20
AREF7: C46.2, U16.20
AREF8: C52.2, U18.20
AREF9: C58.2, U20.20
AREF10: C64.2, U22.20
AREF11: C70.2, U24.20
AREF12: C76.2, U26.20
AREF13: C82.2, U28.20
AREF14: C88.2, U30.20
AREF15: C94.2, U32.20
AREF16: C100.2, U34.20
AREF17: C106.2, U36.20
AREF18: C112.2, U38.20
AREF19: C118.2, U40.20
AREF20: C124.2, U42.20
AREF21: C130.2, U44.20
AREF22: C136.2, U46.20
AREF23: C142.2, U48.20
AREF24: C148.2, U50.20
AREF25: C154.2, U52.20
AREF26: C160.2, U54.20
AREF27: C166.2, U56.20
AREF28: C172.2, U58.20
AREF29: C178.2, U60.20
AREF30: C184.2, U62.20
AREF31: C190.2, U64.20
AREF32: C196.2, U66.20
AREF33: C202.2, U68.20
AREF34: C208.2, U70.20
AREF35: C214.2, U72.20
AREF36: C220.2, U74.20
AREF37: C226.2, U76.20
AREF38: C232.2, U78.20
AREF39: C238.2, U80.20
AREF40: C244.2, U82.20
AREF41: C250.2, U84.20
AREF42: C256.2, U86.20
AREF43: C262.2, U88.20
AREF44: C268.2, U90.20
AREF45: C274.2, U92.20
AREF46: C280.2, U94.20
AREF47: C286.2, U96.20
AREF48: C292.2, U98.20
AREF49: C298.2, U100.20
AREF50: C304.2, U102.20
AREF51: C310.2, U104.20
AREF52: C316.2, U106.20
AREF53: C322.2, U108.20
AREF54: C328.2, U110.20
AREF55: C334.2, U112.20
AREF56: C340.2, U114.20
AREF57: C346.2, U116.20
AREF58: C352.2, U118.20
AREF59: C358.2, U120.20
AREF60: C364.2, U122.20
AREF61: C370.2, U124.20
AREF62: C376.2, U126.20
AREF63: C382.2, U128.20
AREF64: C388.2, U130.20
AREF65: C394.2, U132.20
AREF66: C400.2, U134.20
AREF67: C406.2, U136.20
AREF68: C412.2, U138.20
AREF69: C418.2, U140.20
AREF70: C424.2, U142.20
AREF71: C430.2, U144.20
D1: JP9.1, U4.13
D2: JP7.8, U1.32
D3: JP7.7, U1.1
D4: JP7.6, U1.2
D5: JP7.5, U1.9
D6: JP7.4, U1.10
D7: JP7.3, U1.11
D8: JP7.2, U1.12
D9: JP7.1, U1.13
D10: JP6.12, U1.14
D11: JP9.2, U4.12
D12: JP9.8, U4.32
D13: JP9.7, U4.1
D14: JP9.6, U4.2
D15: JP9.5, U4.9
D16: JP9.4, U4.10
D17: JP9.3, U4.11
D18: JP4.12, U4.14
D19: JP16.1, U6.13
D20: JP16.2, U6.12
D21: JP16.8, U6.32
D22: JP16.7, U6.1
D23: JP16.6, U6.2
D24: JP16.5, U6.9
D25: JP16.4, U6.10
D26: JP16.3, U6.11
D27: JP15.12, U6.14
D28: JP23.1, U8.13
D29: JP23.2, U8.12
D30: JP23.8, U8.32
D31: JP23.7, U8.1
D32: JP23.6, U8.2
D33: JP23.5, U8.9
D34: JP23.4, U8.10
D35: JP23.3, U8.11
D36: JP22.12, U8.14
D37: JP30.1, U10.13
D38: JP30.2, U10.12
D39: JP30.8, U10.32
D40: JP30.7, U10.1
D41: JP30.6, U10.2
D42: JP30.5, U10.9
D43: JP30.4, U10.10
D44: JP30.3, U10.11
D45: JP29.12, U10.14
D46: JP37.1, U12.13
D47: JP37.2, U12.12
D48: JP37.8, U12.32
D49: JP37.7, U12.1
D50: JP37.6, U12.2
D51: JP37.5, U12.9
D52: JP37.4, U12.10
D53: JP37.3, U12.11
D54: JP36.12, U12.14
D55: JP44.1, U14.13
D56: JP44.2, U14.12
D57: JP44.8, U14.32
D58: JP44.7, U14.1
D59: JP44.6, U14.2
D60: JP44.5, U14.9
D61: JP44.4, U14.10
D62: JP44.3, U14.11
D63: JP43.12, U14.14
D64: JP51.1, U16.13
D65: JP51.2, U16.12
D66: JP51.8, U16.32
D67: JP51.7, U16.1
D68: JP51.6, U16.2
D69: JP51.5, U16.9
D70: JP51.4, U16.10
D71: JP51.3, U16.11
D72: JP50.12, U16.14
D73: JP58.1, U18.13
D74: JP58.2, U18.12
D75: JP58.8, U18.32
D76: JP58.7, U18.1
D77: JP58.6, U18.2
D78: JP58.5, U18.9
D79: JP58.4, U18.10
D80: JP58.3, U18.11
D81: JP57.12, U18.14
D82: JP65.1, U20.13
D83: JP65.2, U20.12
D84: JP65.8, U20.32
D85: JP65.7, U20.1
D86: JP65.6, U20.2
D87: JP65.5, U20.9
D88: JP65.4, U20.10
D89: JP65.3, U20.11
D90: JP64.12, U20.14
D91: JP72.1, U22.13
D92: JP72.2, U22.12
D93: JP72.8, U22.32
D94: JP72.7, U22.1
D95: JP72.6, U22.2
D96: JP72.5, U22.9
D97: JP72.4, U22.10
D98: JP72.3, U22.11
D99: JP71.12, U22.14
D100: JP79.1, U24.13
D101: JP79.2, U24.12
D102: JP79.8, U24.32
D103: JP79.7, U24.1
D104: JP79.6, U24.2
D105: JP79.5, U24.9
D106: JP79.4, U24.10
D107: JP79.3, U24.11
D108: JP78.12, U24.14
D109: JP86.1, U26.13
D110: JP86.2, U26.12
D111: JP86.8, U26.32
D112: JP86.7, U26.1
D113: JP86.6, U26.2
D114: JP86.5, U26.9
D115: JP86.4, U26.10
D116: JP86.3, U26.11
D117: JP85.12, U26.14
D118: JP93.1, U28.13
D119: JP93.2, U28.12
D120: JP93.8, U28.32
D121: JP93.7, U28.1
D122: JP93.6, U28.2
D123: JP93.5, U28.9
D124: JP93.4, U28.10
D125: JP93.3, U28.11
D126: JP92.12, U28.14
D127: JP100.1, U30.13
D128: JP100.2, U30.12
D129: JP100.8, U30.32
D130: JP100.7, U30.1
D131: JP100.6, U30.2
D132: JP100.5, U30.9
D133: JP100.4, U30.10
D134: JP100.3, U30.11
D135: JP99.12, U30.14
D136: JP107.1, U32.13
D137: JP107.2, U32.12
D138: JP107.8, U32.32
D139: JP107.7, U32.1
D140: JP107.6, U32.2
D141: JP107.5, U32.9
D142: JP107.4, U32.10
D143: JP107.3, U32.11
D144: JP106.12, U32.14
D145: JP114.1, U34.13
D146: JP114.2, U34.12
D147: JP114.8, U34.32
D148: JP114.7, U34.1
D149: JP114.6, U34.2
D150: JP114.5, U34.9
D151: JP114.4, U34.10
D152: JP114.3, U34.11
D153: JP113.12, U34.14
D154: JP121.1, U36.13
D155: JP121.2, U36.12
D156: JP121.8, U36.32
D157: JP121.7, U36.1
D158: JP121.6, U36.2
D159: JP121.5, U36.9
D160: JP121.4, U36.10
D161: JP121.3, U36.11
D162: JP120.12, U36.14
D163: JP128.1, U38.13
D164: JP128.2, U38.12
D165: JP128.8, U38.32
D166: JP128.7, U38.1
D167: JP128.6, U38.2
D168: JP128.5, U38.9
D169: JP128.4, U38.10
D170: JP128.3, U38.11
D171: JP127.12, U38.14
D172: JP135.1, U40.13
D173: JP135.2, U40.12
D174: JP135.8, U40.32
D175: JP135.7, U40.1
D176: JP135.6, U40.2
D177: JP135.5, U40.9
D178: JP135.4, U40.10
D179: JP135.3, U40.11
D180: JP134.12, U40.14
D181: JP142.1, U42.13
D182: JP142.2, U42.12
D183: JP142.8, U42.32
D184: JP142.7, U42.1
D185: JP142.6, U42.2
D186: JP142.5, U42.9
D187: JP142.4, U42.10
D188: JP142.3, U42.11
D189: JP141.12, U42.14
D190: JP149.1, U44.13
D191: JP149.2, U44.12
D192: JP149.8, U44.32
D193: JP149.7, U44.1
D194: JP149.6, U44.2
D195: JP149.5, U44.9
D196: JP149.4, U44.10
D197: JP149.3, U44.11
D198: JP148.12, U44.14
D199: JP156.1, U46.13
D200: JP156.2, U46.12
D201: JP156.8, U46.32
D202: JP156.7, U46.1
D203: JP156.6, U46.2
D204: JP156.5, U46.9
D205: JP156.4, U46.10
D206: JP156.3, U46.11
D207: JP155.12, U46.14
D208: JP163.1, U48.13
D209: JP163.2, U48.12
D210: JP163.8, U48.32
D211: JP163.7, U48.1
D212: JP163.6, U48.2
D213: JP163.5, U48.9
D214: JP163.4, U48.10
D215: JP163.3, U48.11
D216: JP162.12, U48.14
D217: JP170.1, U50.13
D218: JP170.2, U50.12
D219: JP170.8, U50.32
D220: JP170.7, U50.1
D221: JP170.6, U50.2
D222: JP170.5, U50.9
D223: JP170.4, U50.10
D224: JP170.3, U50.11
D225: JP169.12, U50.14
D226: JP177.1, U52.13
D227: JP177.2, U52.12
D228: JP177.8, U52.32
D229: JP177.7, U52.1
D230: JP177.6, U52.2
D231: JP177.5, U52.9
D232: JP177.4, U52.10
D233: JP177.3, U52.11
D234: JP176.12, U52.14
D235: JP184.1, U54.13
D236: JP184.2, U54.12
D237: JP184.8, U54.32
D238: JP184.7, U54.1
D239: JP184.6, U54.2
D240: JP184.5, U54.9
D241: JP184.4, U54.10
D242: JP184.3, U54.11
D243: JP183.12, U54.14
D244: JP191.1, U56.13
D245: JP191.2, U56.12
D246: JP191.8, U56.32
D247: JP191.7, U56.1
D248: JP191.6, U56.2
D249: JP191.5, U56.9
D250: JP191.4, U56.10
D251: JP191.3, U56.11
D252: JP190.12, U56.14
D253: JP198.1, U58.13
D254: JP198.2, U58.12
D255: JP198.8, U58.32
D256: JP198.7, U58.1
D257: JP198.6, U58.2
D258: JP198.5, U58.9
D259: JP198.4, U58.10
D260: JP198.3, U58.11
D261: JP197.12, U58.14
D262: JP205.1, U60.13
D263: JP205.2, U60.12
D264: JP205.8, U60.32
D265: JP205.7, U60.1
D266: JP205.6, U60.2
D267: JP205.5, U60.9
D268: JP205.4, U60.10
D269: JP205.3, U60.11
D270: JP204.12, U60.14
D271: JP212.1, U62.13
D272: JP212.2, U62.12
D273: JP212.8, U62.32
D274: JP212.7, U62.1
D275: JP212.6, U62.2
D276: JP212.5, U62.9
D277: JP212.4, U62.10
D278: JP212.3, U62.11
D279: JP211.12, U62.14
D280: JP219.1, U64.13
D281: JP219.2, U64.12
D282: JP219.8, U64.32
D283: JP219.7, U64.1
D284: JP219.6, U64.2
D285: JP219.5, U64.9
D286: JP219.4, U64.10
D287: JP219.3, U64.11
D288: JP218.12, U64.14
D289: JP226.1, U66.13
D290: JP226.2, U66.12
D291: JP226.8, U66.32
D292: JP226.7, U66.1
D293: JP226.6, U66.2
D294: JP226.5, U66.9
D295: JP226.4, U66.10
D296: JP226.3, U66.11
D297: JP225.12, U66.14
D298: JP233.1, U68.13
D299: JP233.2, U68.12
D300: JP233.8, U68.32
D301: JP233.7, U68.1
D302: JP233.6, U68.2
D303: JP233.5, U68.9
D304: JP233.4, U68.10
D305: JP233.3, U68.11
D306: JP232.12, U68.14
D307: JP240.1, U70.13
D308: JP240.2, U70.12
D309: JP240.8, U70.32
D310: JP240.7, U70.1
D311: JP240.6, U70.2
D312: JP240.5, U70.9
D313: JP240.4, U70.10
D314: JP240.3, U70.11
D315: JP239.12, U70.14
D316: JP247.1, U72.13
D317: JP247.2, U72.12
D318: JP247.8, U72.32
D319: JP247.7, U72.1
D320: JP247.6, U72.2
D321: JP247.5, U72.9
D322: JP247.4, U72.10
D323: JP247.3, U72.11
D324: JP246.12, U72.14
D325: JP254.1, U74.13
D326: JP254.2, U74.12
D327: JP254.8, U74.32
D328: JP254.7, U74.1
D329: JP254.6, U74.2
D330: JP254.5, U74.9
D331: JP254.4, U74.10
D332: JP254.3, U74.11
D333: JP253.12, U74.14
D334: JP261.1, U76.13
D335: JP261.2, U76.12
D336: JP261.8, U76.32
D337: JP261.7, U76.1
D338: JP261.6, U76.2
D339: JP261.5, U76.9
D340: JP261.4, U76.10
D341: JP261.3, U76.11
D342: JP260.12, U76.14
D343: JP268.1, U78.13
D344: JP268.2, U78.12
D345: JP268.8, U78.32
D346: JP268.7, U78.1
D347: JP268.6, U78.2
D348: JP268.5, U78.9
D349: JP268.4, U78.10
D350: JP268.3, U78.11
D351: JP267.12, U78.14
D352: JP275.1, U80.13
D353: JP275.2, U80.12
D354: JP275.8, U80.32
D355: JP275.7, U80.1
D356: JP275.6, U80.2
D357: JP275.5, U80.9
D358: JP275.4, U80.10
D359: JP275.3, U80.11
D360: JP274.12, U80.14
D361: JP282.1, U82.13
D362: JP282.2, U82.12
D363: JP282.8, U82.32
D364: JP282.7, U82.1
D365: JP282.6, U82.2
D366: JP282.5, U82.9
D367: JP282.4, U82.10
D368: JP282.3, U82.11
D369: JP281.12, U82.14
D370: JP289.1, U84.13
D371: JP289.2, U84.12
D372: JP289.8, U84.32
D373: JP289.7, U84.1
D374: JP289.6, U84.2
D375: JP289.5, U84.9
D376: JP289.4, U84.10
D377: JP289.3, U84.11
D378: JP288.12, U84.14
D379: JP296.1, U86.13
D380: JP296.2, U86.12
D381: JP296.8, U86.32
D382: JP296.7, U86.1
D383: JP296.6, U86.2
D384: JP296.5, U86.9
D385: JP296.4, U86.10
D386: JP296.3, U86.11
D387: JP295.12, U86.14
D388: JP303.1, U88.13
D389: JP303.2, U88.12
D390: JP303.8, U88.32
D391: JP303.7, U88.1
D392: JP303.6, U88.2
D393: JP303.5, U88.9
D394: JP303.4, U88.10
D395: JP303.3, U88.11
D396: JP302.12, U88.14
D397: JP310.1, U90.13
D398: JP310.2, U90.12
D399: JP310.8, U90.32
D400: JP310.7, U90.1
D401: JP310.6, U90.2
D402: JP310.5, U90.9
D403: JP310.4, U90.10
D404: JP310.3, U90.11
D405: JP309.12, U90.14
D406: JP317.1, U92.13
D407: JP317.2, U92.12
D408: JP317.8, U92.32
D409: JP317.7, U92.1
D410: JP317.6, U92.2
D411: JP317.5, U92.9
D412: JP317.4, U92.10
D413: JP317.3, U92.11
D414: JP316.12, U92.14
D415: JP324.1, U94.13
D416: JP324.2, U94.12
D417: JP324.8, U94.32
D418: JP324.7, U94.1
D419: JP324.6, U94.2
D420: JP324.5, U94.9
D421: JP324.4, U94.10
D422: JP324.3, U94.11
D423: JP323.12, U94.14
D424: JP331.1, U96.13
D425: JP331.2, U96.12
D426: JP331.8, U96.32
D427: JP331.7, U96.1
D428: JP331.6, U96.2
D429: JP331.5, U96.9
D430: JP331.4, U96.10
D431: JP331.3, U96.11
D432: JP330.12, U96.14
D433: JP338.1, U98.13
D434: JP338.2, U98.12
D435: JP338.8, U98.32
D436: JP338.7, U98.1
D437: JP338.6, U98.2
D438: JP338.5, U98.9
D439: JP338.4, U98.10
D440: JP338.3, U98.11
D441: JP337.12, U98.14
D442: JP345.1, U100.13
D443: JP345.2, U100.12
D444: JP345.8, U100.32
D445: JP345.7, U100.1
D446: JP345.6, U100.2
D447: JP345.5, U100.9
D448: JP345.4, U100.10
D449: JP345.3, U100.11
D450: JP344.12, U100.14
D451: JP352.1, U102.13
D452: JP352.2, U102.12
D453: JP352.8, U102.32
D454: JP352.7, U102.1
D455: JP352.6, U102.2
D456: JP352.5, U102.9
D457: JP352.4, U102.10
D458: JP352.3, U102.11
D459: JP351.12, U102.14
D460: JP359.1, U104.13
D461: JP359.2, U104.12
D462: JP359.8, U104.32
D463: JP359.7, U104.1
D464: JP359.6, U104.2
D465: JP359.5, U104.9
D466: JP359.4, U104.10
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
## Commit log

2014-01-23 updated readme
    added image, links, description, authors
2014-01-23 initial commit of hardware (v13)
2014-01-23 moved al FPs to 0603
    Also fixes all the angle errors in traces coming off of IC.
2014-01-23 updated frame in SCH
2014-01-24 Added power isolation jumper
2014-01-24 added gitignore and cleanup batch files
2014-01-31 footprint updates, schematic work
    -reset button, moved pads out for more toe
    -resonator, 1:1 with fake traces
    -moved all labels to flags in sch
    -moved A6/A7 header to 2X1, rather than singles
2014-02-06 deleted eagle backup files
2014-02-06 v14 ready for protos
    changed led footprint to cloaser to true 0603
2014-02-26 Created Giant Panel v14
2014-04-09 Updating README
2015-06-22 Updating directory name to prevent OS errors
2015-08-20 Adding Pro Mini graphical datasheets
2015-09-22 Updating graphics files, deleting windows script(redundant with .git files)
2016-07-18 Created first draft eagle files with silk graphics
2016-07-20 Tuned up silk
2016-07-21 Finished design review and checklist
2016-08-02 Updated schematic to standard
2016-08-11 Fixed schematic issues
2016-08-15 Re-imported silk graphics, moved a couple ground vias, incremented version number to 1.6
2016-08-15 Post review and checklist verification
2016-08-17 Added dual-part SKU information in schematic
2016-09-13 Incremented version numbers
2016-09-15 Expanded ordering instructions
2019-03-29 Correct Port Name on Pin 10
    - Corrected pin name from "PCB2" to "PB2"
    - Rename files based on the correction
